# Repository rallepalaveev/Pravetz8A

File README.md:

This is the motherboard for the Pravetz 8A computer with a mod that CM633 can be replaced by g16v8.

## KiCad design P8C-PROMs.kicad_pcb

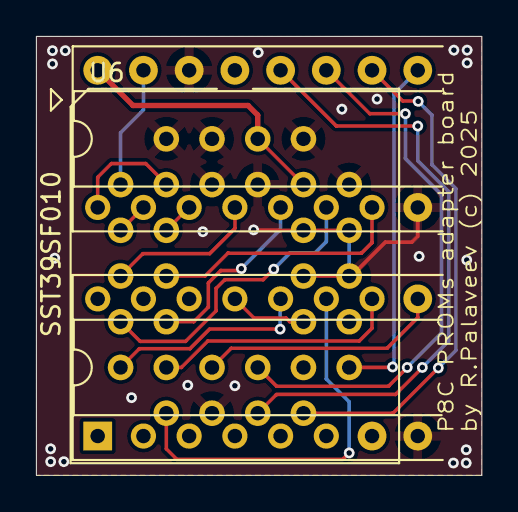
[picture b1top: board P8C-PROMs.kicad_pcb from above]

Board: 2 copper layers, 24.7 x 24.4 mm, 3 parts (0 on the bottom side), 19 nets.

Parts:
U1: PROM-H; DIP-16_W7.62mm_Socket
U2: PROM-L; DIP-16_W7.62mm_Socket
U6: SST39SF010; PLCC-32_THT-Socket

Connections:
+5V: U1.16, U6.31, U6.32
D0: U2.12, U6.13
D1: U2.11, U6.14
D2: U2.10, U6.15
D3: U2.9, U6.17
D4: U1.12, U6.18
D5: U1.11, U6.19
D6: U1.10, U6.20
D7: U1.9, U6.21
FA0: U1.5, U6.12
FA1: U1.6, U6.11
FA2: U1.7, U6.10
FA3: U1.4, U6.9
FA4: U1.3, U6.8
FA5: U1.2, U6.7
FA6: U1.1, U6.6
FA7: U1.15, U6.5
GND: U1.8, U1.14, U2.8, U2.14, U6.1, U6.2, U6.3, U6.4, U6.16, U6.22, U6.23, U6.25, U6.26, U6.27, U6.28, U6.29, U6.30
~OE: U2.13, U6.24

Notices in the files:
P8C-PROMs.kicad_pcb:
by R.Palaveev (c) 2025
